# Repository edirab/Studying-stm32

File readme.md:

### Лабораторные по программированию stm32 в рамках курса 
#### *"Интеллектуальные системы в мехатронике и робототехнике"*

Используемое ПО:

1. Конфигуратор CubeMX (https://www.st.com/en/development-tools/stm32cubemx.html)
2. Среда CubeIDE (https://www.st.com/en/development-tools/stm32cubeide.html)
3. Утилита для прошивки CubeProg (https://www.st.com/en/development-tools/stm32cubeprog.html)
4. Serial Terminal от Eltima Software
5. Saleae Logic 1.2.18
6. Библиотека HAL

- **Лабораторная №1** с.13 Мигание светодиодом по таймеру, вариант 4
- **Лабораторная №2** с.31 Изучение АЦП, программная реализация ШИМ, вариант 4
- **adc_to_pwm-1** Аппаратное управление ШИМ, другие варианты

- **Лабораторная №3** с.43 Построение разомкнутой системы управления ДПТ
- **Лабораторная №4** с.47 Построение замкнутой системы управления ДПТ
- **Лабораторная №5** с.49 Исследование нейросетевого регулятора
- **Приложение А** с.50 Программа для ознакомления с модулями RCC, GPIO, TIM
- **Приложение Б** с.52 Программа для ознакомления с модулями МПС ADC и таймером в режиме формирования ШИМ

***

***

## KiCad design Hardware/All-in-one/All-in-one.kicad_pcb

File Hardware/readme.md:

## Схемы электрические и чертежи печатных плат проектов и их модулей

### Модули клавиатуры
- Фильтр на RC-цепочке

- Триггер Шмитта

- Триггер Шмитта вер. 2

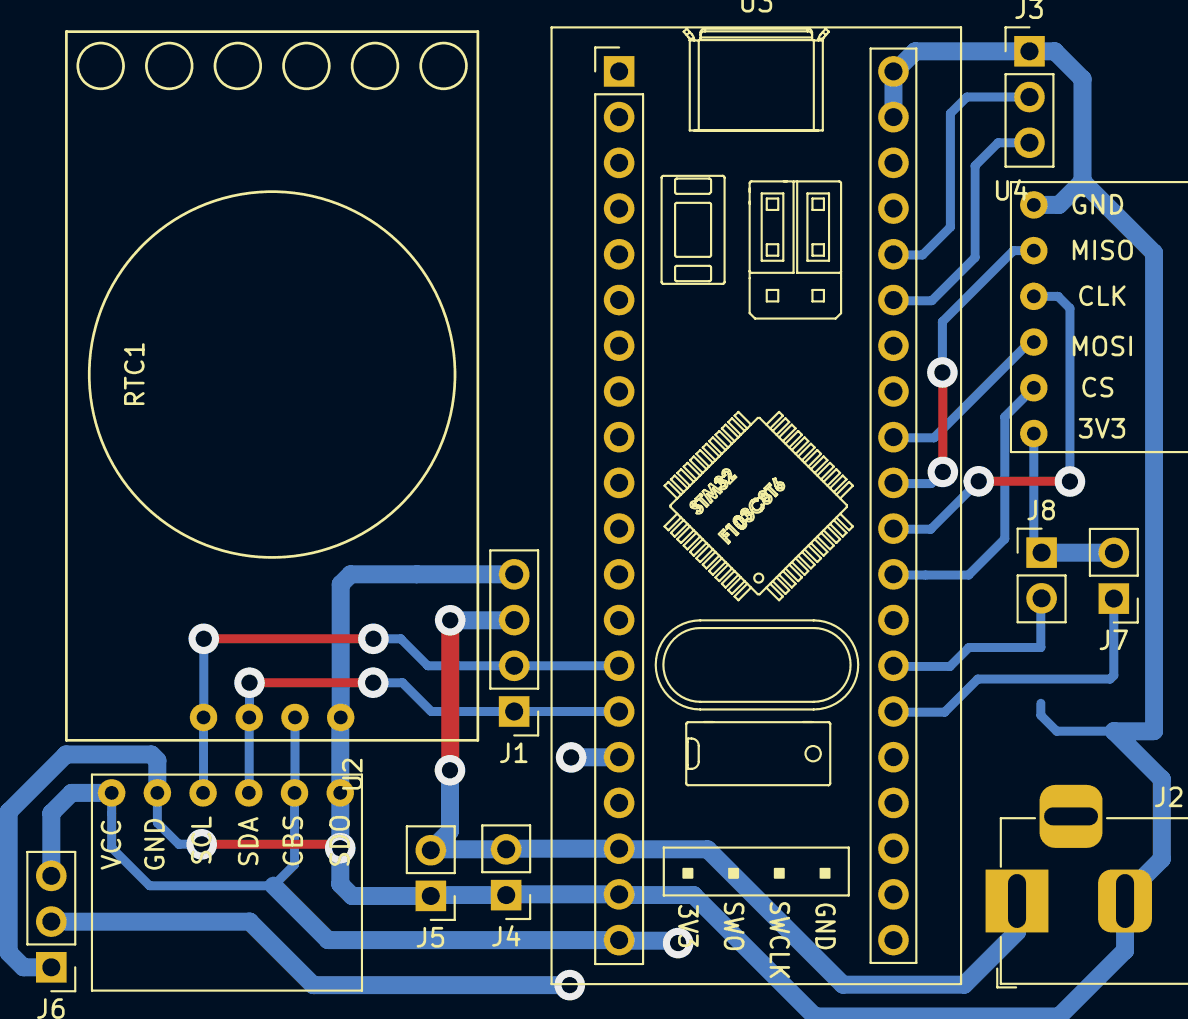
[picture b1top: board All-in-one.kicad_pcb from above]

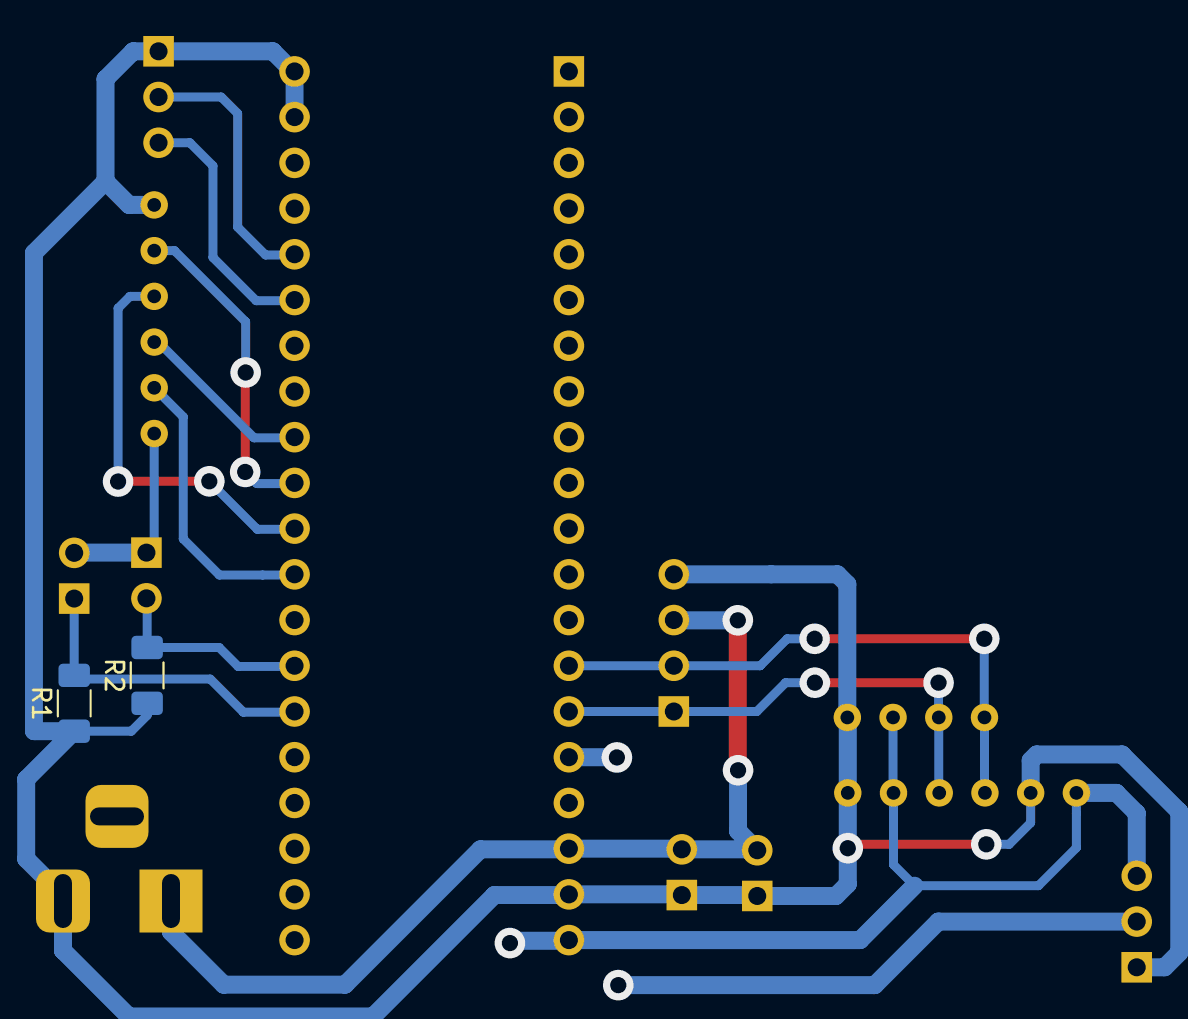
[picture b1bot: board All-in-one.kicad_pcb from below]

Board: 2 copper layers, 14 parts (2 on the bottom side), 14 nets.

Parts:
J1: Conn_01x04_Male; PinHeader_1x04_P2.54mm_Vertical
J2: Barrel_Jack; BarrelJack_Horizontal
J3, J6: Conn_01x03; PinHeader_1x03_P2.54mm_Vertical
J4, J5, J7, J8: Conn_01x02_Male; PinHeader_1x02_P2.54mm_Vertical
R1, R2: 10k; R_1206_3216Metric_Pad1.30x1.75mm_HandSolder
RTC1: RTC_DS3231
U2: BMP280_flipped
U3: YAAJ_BluePill_Part_Like; YAAJ_BluePill_1
U4: microSD_flipped; microSD_Card_3V3

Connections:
3V3: J6.3, J7.2, J8.1, RTC1.2, U2.2, U2.6, U3.20, U3.38, U4.6
+5V: J1.3, J2.1, J4.2, J5.2, U3.18
A1: J7.1, R1.2, U3.26
A2: J8.2, R2.2, U3.27
DHT_11: J6.2, U3.16
GND: J1.4, J2.2, J3.1, J4.1, J5.1, J6.1, R1.1, R2.1, RTC1.1, U2.1, U2.5, U3.19, U3.39, U3.40, U4.1
I2C1_SCL: J1.2, RTC1.4, U2.4, U3.14
I2C1_SDA: J1.1, RTC1.3, U2.3, U3.15
unnamed: J3.2, U3.36
unnamed: J3.3, U3.35
unnamed: U3.29, U4.5
unnamed: U3.30, U4.3
unnamed: U3.31, U4.2
unnamed: U3.32, U4.4

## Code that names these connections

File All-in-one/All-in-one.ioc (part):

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Mcu.Name=STM32F103C(8-B)Tx
Mcu.Package=LQFP48
Mcu.UserName=STM32F103C8Tx
PA0-WKUP.Signal=ADCx_IN0
PA1.Signal=ADCx_IN1
PA13.Mode=Serial_Wire
PA13.Signal=SYS_JTMS-SWDIO
PA14.Mode=Serial_Wire
PA14.Signal=SYS_JTCK-SWCLK
PA2.Signal=ADCx_IN2
PA4.Mode=NSS_Signal_Hard_Output
PA4.Signal=SPI1_NSS
PA5.Mode=Full_Duplex_Master
PA5.Signal=SPI1_SCK
PA6.Mode=Full_Duplex_Master
PA6.Signal=SPI1_MISO
PA7.Mode=Full_Duplex_Master
PA7.Signal=SPI1_MOSI
PB0.GPIOParameters=GPIO_Label
PB0.GPIO_Label=Debug_LED_Y
PB0.Signal=GPIO_Output
PB1.GPIOParameters=GPIO_Label
PB1.GPIO_Label=Debug_LED_G
PB1.Signal=GPIO_Output
PB10.Mode=Asynchronous
PB10.Signal=USART3_TX
PB11.Mode=Asynchronous
PB11.Signal=USART3_RX
PB3.GPIOParameters=GPIO_PuPd,GPIO_Label,GPIO_ModeDefaultEXTI
PB3.GPIO_Label=Set
PB3.GPIO_ModeDefaultEXTI=GPIO_MODE_IT_FALLING
PB3.GPIO_PuPd=GPIO_PULLUP
PB3.Signal=GPXTI3
PB4.GPIOParameters=GPIO_PuPd,GPIO_Label,GPIO_ModeDefaultEXTI
PB4.GPIO_Label=Minus
PB4.GPIO_ModeDefaultEXTI=GPIO_MODE_IT_FALLING
PB4.GPIO_PuPd=GPIO_PULLUP
PB4.Signal=GPXTI4
PB5.GPIOParameters=GPIO_PuPd,GPIO_Label,GPIO_ModeDefaultEXTI
PB5.GPIO_Label=Plus
PB5.GPIO_ModeDefaultEXTI=GPIO_MODE_IT_FALLING
PB5.GPIO_PuPd=GPIO_PULLUP
PB5.Signal=GPXTI5
PB6.Mode=I2C
PB6.Signal=I2C1_SCL
PB7.Mode=I2C
PB7.Signal=I2C1_SDA
PB8.GPIOParameters=GPIO_Label
PB8.GPIO_Label=DHT_11
PB8.Signal=GPIO_Output
PD0-OSC_IN.Mode=HSE-External-Oscillator
PD0-OSC_IN.Signal=RCC_OSC_IN
PD1-OSC_OUT.Mode=HSE-External-Oscillator
PD1-OSC_OUT.Signal=RCC_OSC_OUT
RCC.SYSCLKFreq_VALUE=72000000
RCC.SYSCLKSource=RCC_SYSCLKSOURCE_PLLCLK
board=custom

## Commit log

2020-05-12 initial
2020-05-12 Фильтрация выбором наименьшего из 4-х, но этого всё ещё не достаточно. Выборосы с АЦП на сверхмалых напряжениях (0.16 - 0.2 В). Добавлен readme и папка с литературой и даташитами
2020-05-12 Обновлён readme
2020-05-12 readme 2
2020-12-30 Finally удалось подключить sd-карту к контроллеру STM32F103C8T6. Все модули на 5 Вольт рабочие. Карту необходимо форматировать как FAT, объём - не более 4 Гб (большие объёмы не проверены)
2020-12-31 Иследование размера прошивки и оптимизация потребления flash-памяти. Добавлен пример проекта работы с LCD-дисплеем 16х2
2021-01-01 1. Проверена работоспособность проектов: - DHT11_v1 - LCD_I2C_F103 - I2C_DS3231
    2. Выяснен адрес дисплея.
    3. Устранена неоднородность в использовании различных UART в разных проектах. Теперь используем
    UART3 (PB10, PB11)
    4. Добавлено описание используемых выводов в основной readme
    В целом, по частям всё работает, осталось грамотно скомпановать в единый проект;
    код проекта I2C_DS3231 нуждается в рефакторинге.
2021-01-01 Добавлен даташит на расширитель портов i2c LCD-дисплея. Выяснилось, что у stm32 f103 c8t6 нет календаря in hardware, необходимо использовать отдельный модуль. Переключение проекта SD_CARD_SPI_F103C8/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
2021-01-03 Протестирован модуль SD-карты на 3,3В, исправлена проблема с аппаратным выбором ~CS Добавлены примеры ддя stm-8
2021-01-04 Начало нового проекта по объединению всех кусочков
2021-01-04 Добавлены файлы для датчика влажности и температуры, а также часов реального времени
2021-01-04 Миграция на CubeMX 6.1.1
2021-01-05 Добавлен файл с функциями для работы с дисплеем. Добавлен флаг компоновщика "-u -fprintf_float", сожрал очень много Flash'a Карта памяти в новом проекте пока не работает, исгналов на выходе нет вообщ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
2021-01-09 - Миграция проекта SD_CARD_SPI_F103C8/. Всё работает) - Проект All-in-one/ теперь способен взаимодействовать с картой памяти, еее!! + Разгадана тайна файлов fatfs_sd.c(h): это пользовательская реализ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
2021-01-10 - Найдена причина по которой DHT11 переставал откликаться вскоре после запуска: изменено время удержания мастером линии в низком уровне для инициации передачи с 15 на 20 мс. Теперь датчик отвечает че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
2021-01-23 Добавлена документация на датчики BME 280 & BMP 280
2021-01-24 - Найден пример опроса BMP280, код интегрирован в общий проект. - Написан колхозный метод для установки даты и времени часов TODO: Необходимо разобраться с лишними буферами, оставшимися от других при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
2021-01-24 - Перекомпанован код для правильной последовательности измерений - Добавлена дополнительная задержка считывания показаний влажности с DHT: теперь эта скотина опрашивается лишь раз в 3 секунды. Так ра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
2021-01-24 - Удобная структура для хранения времени - Добавлены дни недели - Убраны лишние переменные
2021-01-24 - Данные не записывались на карту без вызова flush - Дописан All-in-one/readme.md TODO: кнопки для настройки часов
2021-01-25 - Добавлены 3 кнопки для настройки часов и их обработка по прерываниям - Индикация процесса настройки миганием с помощью конечного автомата - Для работы задержек в прерывании необходимо было понизить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
2021-01-25 - Добавлен аналоговый датчик влажности почвы, небольшие правки гарфического интерфейса - Исследован диапазон изменения значения датчика влажности почвы
2021-01-26 - Добавлено сохранение настроенного времени - Выяснено, почему при вычитании из 00 получается 15: 00 - 1 = 255, 255%60 = 15 - Необходимо аппаратное подавление дребезга кнопок. Иногда контроллер завис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
2021-01-26 - АЦП для измерения показаний с фоторезисторов, - Замер длительности основного цикла и передачи данных по SPI - Небольшой рефакторинг для удобства
2021-01-28 Начало проекта печатной платы
2021-02-06 - Модуль клавиатуры keyboard_v1/ давно сделан - Проект по изучению внешних прерываний: Ext_Interrups/ && Ext_Interrups_v2/ - Два контроллера F103C8T6 - неоригинальные!! - Добавлена документация по F3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
2021-02-06 - Разведена печатная плата под keyboard_v2/ - Изменена структура каталогов глобально
2021-02-06 - Добавлен русский словарь для проверки орфографии согласно (https://sys-adm.in/programming/341-eclipse-russian-language-support.html) - Установлена кодировка UTF-8 по умолчанию, символы конца строки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
2021-02-07 Распаян модуль keyboard_v2/
2021-02-09 - Разработка модуля keyboard_v3/. Меньше кнопок, кнопки крупнее, дорожки толще
2021-02-09 Распаян и протестирован модуль клавиатуры keyboard_v3/. Можно приступить к доработке основного приложения
2021-02-09 Надлежащее переименование директории
2021-02-11 - Начало проекта по использованию внутренних часов реального времени с пересчётом из Unix-даты в григорианскую - Выяснилось, что используемый модуль DS3231 неисправен. Частота на выходе 32k составляе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
2021-02-12 - Доработана система меню проекта All-in-one/: сброс секунд по нажатию как "+", так и "-", настройка дня недели. Отсчёт дней недели - с воскресенья. Провеняем точность хода часов. Всё ещё встречаются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
2021-02-12 Схема электрическая принципиальная All-in-one/
2021-02-14 Добавление IWDT с периодом 1,2 с
2021-02-14 Инициализационный код теперь в виде пар *.c && *.h-файлов
2021-02-14 - Исправлен баг с отображением дня недели SUN - Переключение срабатывания прерываний по фронту вместо спада в связи с ниличием триггера Шмитта - Увеличина скорость работы ножки DHT_11
2021-02-14 Ещё раз исправлен баг с днём недели. Протестирована работа сторожевого таймера
2021-02-14 Теперь счётчик предотвращает зависание в цикле настройки часов. Таймаут бездействия пользователя - 30 секунд
2021-02-14 Продолжаем разводить п.п. На морозе часы неожиданно сбросились. справлени баг со слишком ранним выходом из режима настройки часов. 30 секунд недостаточно, чтобы точно сбросить секунды
2021-02-14 Добавлена четвёртая кнопка "X10" на вывод PA15
